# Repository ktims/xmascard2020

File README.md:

# Merry Christmas 2020! 🎄🎁

If you're here, it's probably because I sent you a card/ornament and you can't get it to work, thought it might be fun to hack on, or you were curious how it was designed. Unless it's the first one, awesome!!

This was a vague idea in my head on Dec 4th, sent for manufacturing on Dec 6th, and if I managed to get it to you before Christmas, considering my projects usually go on for years and never really get 'finished', I'm super impressed with myself. Guys, I actually finished a project!! It's been a 'sprint'! I hope you enjoy it 😁.

If you just want to get hacking, download [PlatformIO](https://platformio.org/platformio-ide), check out the repo, and have a look at `code/include/Effects.h`. The only other thing you need is a 3.3V USB-serial adapter ('FTDI') and some dupont wires to hook it up. The `/code` README has more information on how to flash the board, and how the firmware works. PIO makes it super easy to set up the development environment, it's like one click, don't be scared!!

## Usage

### User Interface

There's really just one button, on the back near the top of the board and not labelled because I'm dumb. When off, press once briefly to turn on. When on, a long-press will enter brightness setting mode, and a short press will rotate between brightnesses. A long-press again will go back to normal operation. Hold for 5s and release to turn off.

You can ignore the PROG button entirely unless you're planning to hack on the firmware, it does nothing other than put it into programming mode on power up.

If untouched for ~4h it will power itself off.

### Power

**Batteries**: Battery life should be approx 30 hours while operating. After the season I suggest removing the batteries as they will run down slowly over time since there is no hard power switch (a couple years). If you need more batteries, they are readily available type CR2032. Find them at the dollar store or on Amazon. The PKCELL ones I sent are cheap on Amazon and seem to not be trash.

**External power**: 🔴🔴 **NOTE: Don't supply external power with batteries installed!** 🔴🔴 In theory you could power this with any 4-16VDC supply (@ 10mA or so). It should run reliably at 5V though, so a cheerful USB charger would be perfect. There's an external power connector on the back of the board; if I thought you might want to hook this up, I included a pigtail with the appropriate connector already on it. The connector is a JST-PH (2.0mm pitch). +/- as marked on the board.

## Design
### Hardware

Goals / Met?:
* **Cheap** / Total cost incl. expedited shipping for 10 boards was \$153 (\$15.30 ea). I think so, though I would've liked to see $10.
* **Entirely manufactured/assembled by JLCPCB** / Mostly. LEDs were hand assembled, but I didn't expect them to be manufacturable anyway as they are mounted upside down.
* **Slim for mailing** / Yes
* **Battery life >= 24h with standby life of > 1 month** / Measured operating current with the included effects at full brightness is ~4-7mA. With 220mA CR2032s, that should be 30-50h. Standby current is <5µA, which is longer than the 3y shelf-life of the batteries.
* **Light/balanced enough with batteries to hang comfortably on a tree, or sit on a small stand** / Seems to work well for me.

#### Tools

I use [KiCad EDA](https://kicad.org/) exclusively for hardware design. [Inkscape](https://inkscape.org/) was used to create the simple artwork on the silkscreen and place the LED drill hits, with [Svg2Shenzhen](https://github.com/badgeek/svg2shenzhen) to export to Kicad. [FreeCAD](https://www.freecadweb.org/) was used for 3D modeling of the stand.

#### Design decisions

##### Power supply

It needed to be battery powered, as there is no standard power source in a Christmas tree. I considered hacking in to LED christmas light bulbs to tap power, but there doesn't seem to be a standard for these and it's not a convenient way to tap power anyway, since they seem to usually be wired in series, which would require a shunt supply, and are AC which complicates too. Same problems with old-fashioned incandescents.

Which really left two choices - coin cell(s) or AAAs. AAAs have much more capacity, but have two major issues for this design: the voltage dropped over the driver and LED would require at least 3 cells (3.5V bare minimum, when near empty) or a boost converter. 3 cells (even 2) wouldn't fit within the PCB envelope, and they would be relatively heavy and likely to make it hang funny or require a large stand. So it'd have to be a single-cell solution - possible with a fancy specialized boost converter, but expensive and relatively bulky (see 'cheap' and 'slim' design goals).

I considered taping a small lithium-ion cell to the back and including a USB charger on board, but these cells are not readily available in North America and the slow boat would be too slow in this case. JLCPCB also won't assemble USB connectors, and both these and the batteries are kinda expensive. I'm not *sure* the voltage would be sufficient, either.

So two coin cells (to maximize capacity and get to the necessary voltage) it is, in the largest standard format that I could cram on the board. The disposable-ness and temporary-usefullness of this choice doesn't make me happy, but I suppose it's a bit of a disposable and temporary item anyway 😕.

Maybe the 2021 version will do something more graceful here and attempt a life beyond the holiday season 😈.

##### Microcontroller

Basically I just picked the cheapest thing on the JLCPCB Basic Parts list that I was familiar with (STM32, AVR, or MSP430) and made sure it would do the job (really the only thing that mattered much was the standby power consumption, and that it could generate a 4MHz output clock for the MBI's PWM). It is an STM32F030F4 with 16KB flash and 4KB RAM and can run at up to 48MHz. Power consumption is linear with clock rate, so I will run it at 8MHz, which is as slow as possible to be able to generate a 4MHz clock for the MBI5043 to get complete PWM cycles at 60fps (65536 * 60 = 3.93MHz). I could run it faster since it sleeps when not actively drawing a frame, and it could be similar consumption or even save power, while offering increased processing power for fancy effects (what, though?), but it will probably just make it more power hungry. Thanks physics.

##### LED Driver

I wanted at least 10 constant-current outputs, at least 10-bit PWM, and a SPI-ish interface (I2C is slow, a pain to bit-bang, and power hungry). Considering JLCPCB's parts list, the only candidate really was Macroblock MBI5043. It has a weird interface for the latch that precludes use of the hardware SPI peripheral, and not a great datasheet, but it seems simple enough to bit-bang.

##### Power control

Toggle switches are relatively expensive and can't be placed by JLCPCB assembly service, so I preferred to avoid them. That means soft power, and to minimize parts, it means the microcontroller must have a standby mode with current consumption in low µA that can wake from a button press. The STM32F030 does so (~1.7µA). It also means everything else including the 3.3V regulator and LED driver must have a low current in standby too. Hence the selection of slightly more expensive HT7533 regulator, and using a P-channel power switch for the LED driver which has no standby mode and current consumption of several mA with all LEDs off (it may be less in practice without the PWM clock running). This also enables auto-power-off.

When powered down, standby consumption comes from HT7533 (2.5µA) + STM32 (1.7µA) + Q1 leakage (100nA) is ~4.5µA standby current. This should give ~5 years standby battery life. Good enough for this purpose. The traditional 'jellybean' 1117 regulator consumes 4mA, and without the power switch on the MBI5043 (guessing 2-4mA from the datasheet), it'd probably barely last a day.

### Software

#### Toolchain / Environment

* [PlatformIO](https://platformio.org/) build tools, to make hacking more accessible and build setup easy
* [libopencm3](https://github.com/libopencm3/libopencm3) 'convenience' library to interface with the STM32 peripherals (note: PIO will pull this for you automatically). I've used this before. It's nothing special, and for what little I'm using of it here, probably didn't save much time over just writing the registers. But time is time. Sorry, I don't know Arduino and its approach is too high level for me.
* [C++17](https://en.cppreference.com/w/cpp/17). I almost tried [Rust](https://www.rust-lang.org/what/embedded) for this, but opted for something I knew at least a little bit of (and that you might know a little bit of too) due to the crunch. Sorry, you can't run Node on this hardware.

#### Structure

See `code/README.md` for more information.

The structure is fairly typical of embedded programs. Execution is driven by a 1/60s timer interrupt, which wakes the processor from sleep. The ISR for this interrupt sends a frame to the LED driver if one is ready, and the mainloop then executes to draw the next frame and handle the button. After that works is complete, the processor goes back to sleep to wait for the next frame time.

I originally envisioned swapping function pointers to implement the effects, but in classic over-engineered fashion, this lead to templated callable structs that inherit from a base `MBIEffect` class and use dynamic dispatch. Why not.

There's not much else of interest there, but I welcome harsh code reviews.

## Mistakes / Unexpectedness

* I sprung for fancy Immersion Gold finish PCBs because they'd look nicer, even though there's barely any exposed copper on the front. I should have realized this could be used for the artwork and gold-on-black would be much blingier than white-on-black, or even 3-colour art!
* I did not think to match the LED reference designations with their output # / buffer index. At least it's only an off-by-one since the references are 1-indexed rather than random.
* 3 weeks is not enough time to design boards, have them made and delivered, write software, and then deliver to recipients. Not enough time *at all*.
* Read the datasheets *carefully*. The pin I wired up as the PWM clock does indeed operate as a timer output, but only on some device variants, and not the one I have. Could've just used one of the free pins instead...this is why there is a bodge wire on your board.
* These 'lighting' LEDs are...melty... They tolerate almost no heat from the soldering iron. Not used to components being made with thermoplastics.

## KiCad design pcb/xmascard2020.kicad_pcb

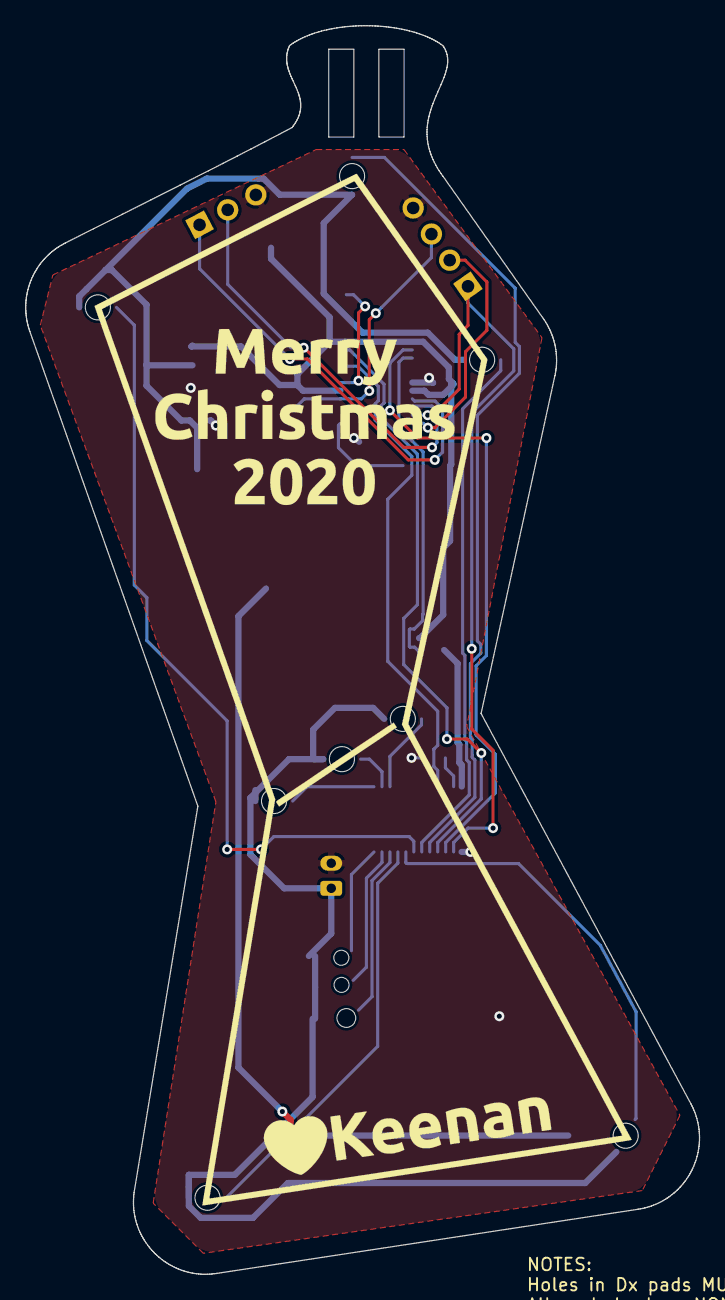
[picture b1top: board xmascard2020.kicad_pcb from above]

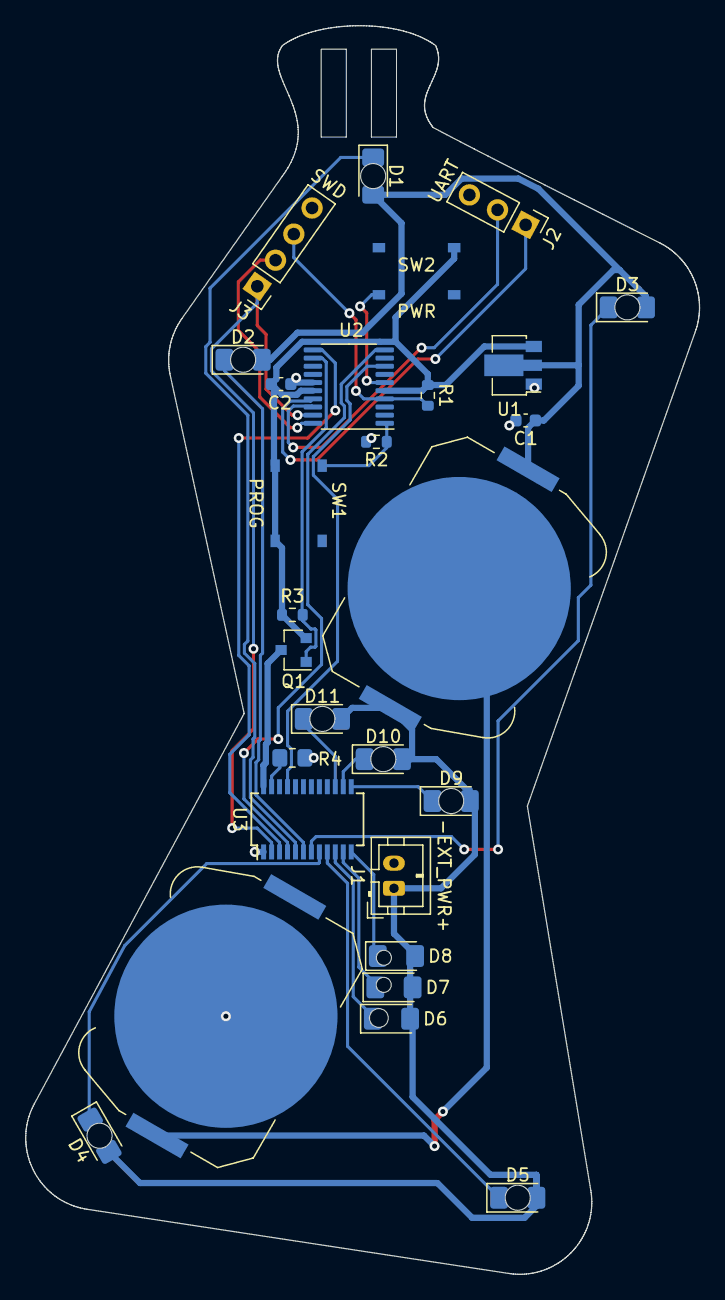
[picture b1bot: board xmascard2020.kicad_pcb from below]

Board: 2 copper layers, 53.7 x 99.6 mm, 29 parts (28 on the bottom side), 28 nets.

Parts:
ARTWORK: Val**; orion
BT1, BT2: CR2032; BatteryHolder_Keystone_3034_1x20mm
C1, C2: 10u; C_0603_1608Metric
D1, D2, D3, D4, D5, D6, D7, D8, D9, D10, D11: LED; LED_1206_3216Metric_Pad1.42x1.75mm_HandSolder
J1: -EXT_PWR+; JST_PH_B2B-PH-K_1x02_P2.00mm_Vertical
J2: UART; PinHeader_1x03_P2.54mm_Vertical
J3: SWD; PinHeader_1x04_P2.54mm_Vertical
Q1: AO3401A; SOT-23
R1, R2, R3: 100k; R_0603_1608Metric
R4: 2.8k; R_0805_2012Metric_Pad1.20x1.40mm_HandSolder
SW1: PROG; TS-1187A
SW2: PWR; TS-1187A
U1: HT7533-1; SOT-89-3
U2: STM32F030F4Px; TSSOP-20_4.4x6.5mm_P0.65mm
U3: MBI5043GP; SSOP-24_3.9x8.7mm_P0.635mm

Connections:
+3V3: C2.1, Q1.2, R1.1, R3.2, SW1.1, SW2.2, U1.3, U2.5, U2.16
+6V: BT1.1, C1.1, D1.2, D2.2, D3.2, D4.2, D5.2, D6.2, D7.2, D8.2, D9.2, D10.2, D11.2, J1.1, U1.2
/RX: J2.2, U2.18
/SWCLK: J3.2, U2.20
/SWDIO: J3.1, U2.19, U3.2
/TX: J2.1, U2.17
/~RESET: J3.3, R1.2, U2.4
GND: BT2.2, C1.2, C2.2, J1.2, J2.3, J3.4, R2.2, R4.2, U1.1, U2.15, U3.1
unnamed: BT1.2, BT2.1
unnamed: D1.1, U3.5
unnamed: D2.1, U3.6
unnamed: D3.1, U3.7
unnamed: D4.1, U3.8
unnamed: D5.1, U3.9
unnamed: D6.1, U3.10
unnamed: D7.1, U3.11
unnamed: D8.1, U3.12
unnamed: D9.1, U3.13
unnamed: D10.1, U3.14
unnamed: D11.1, U3.15
unnamed: Q1.1, R3.1, U2.12
unnamed: Q1.3, U3.24
unnamed: R2.1, SW1.2, U2.1
unnamed: R4.1, U3.23
unnamed: SW2.1, U2.6
unnamed: U2.8, U3.21
unnamed: U2.10, U3.4
unnamed: U2.11, U3.3

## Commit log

2020-12-14 Initial commit of all the things
2020-12-16 Add datasheets to repo
2020-12-16 refactor rng to separate sourcefile
2020-12-17 Add initial README
2020-12-17 Add 3d model to pushbutton footprint
2020-12-18 Add leaflet document
2020-12-18 PDF of leaflet only needs 1 copy, not 12
2020-12-18 Add 3D renders of front and back of board
2020-12-18 Add 'stand' manufacturing artifacts
2020-12-21 Release version 1.0
2020-12-22 Add production outputs to repo
2020-12-23 Update documentation
2020-12-23 Improved comments
